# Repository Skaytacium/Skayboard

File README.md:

# Skayboard

## What?

Its **Skay**tacium's key**board**.

## Why? (I get this one a lot)

Good question.

## Layout?

[Here](http://www.keyboard-layout-editor.com/#/gists/023afb41bbd40c8d3c89d3bae84d59ea).

## Really, why?

I couldn't find a keyboard which had this exact layout (some suggested a 60% + numpad, do you think I'm sensible?).  
I also found the pre-existing PCBs too expensive and the open source ones had goofy layouts.  
I'm jobless, stupid and I regret everything.

## And?

- The `sk` keys are macro keys.
- It uses [QMK](https://qmk.fm/).
- Uses [SK6812 Mini-E](https://cdn-shop.adafruit.com/product-files/4960/4960_SK6812MINI-E_REV02_EN.pdf) LEDs, hand solder them if you want to, connection matrix [here](#connections) (because the name starts with SK).
+ The Skaytacium way to build one would be:
  - C<sup>3</sup>Equalz Tangerines, light green (52g)
  - 5mm acrylic plate
  - Stacked crylic and aluminum (layered)
- It took me ~~2~~ 3 years to make this (check earliest commit) because of the global chip shortage and doomerism.

## Details?

### PCB?
- 2 layer
- 355x107 mm
- AVR (32U4), keeping it as simple as possible.
	+ There is no ESD, overcurrent or surge protection on the PCB. I assume all modern electronic USB ports to compensate for that.
- Pads made for handsoldering.
- Curved traces, because the 90s were cool.
- **Not attached to the case in any way, only to the plate, allows for more customizable mounting options.**
- `svg` and `dxf` files for reference are in `lib/gen`.

#### Renders?
- Front

- Back

- Front populated

### Plate?
- Desgined for 5mm plates, but can be used for 3mm-5mm.
	+ 1.5mm should also be possible, but it is strongly not recommended to use that.
- Who am I to tell you though, go crazy with it, `dxf` file is in `lib/gen`.

#### Renders?

### Case?
- Stacked in the following order:
	+ Spacer (L2)
	+ Plate (PCB has no connection to the case)
	+ Spacer (L1)
	+ Spacer (L0)
	+ Case & Logo
- **IMPORTANT:** Spacers L1 and L0 should have atleast 6mm of total height due to the oscillator being an HC49, and that requires 4mm clearance + 1.6mm clearance for PCB thickness.
- **ALSO IMPORTANT:** Either one of spacers L1 or L0 have to be transparent, otherwise you won't be able to see the underglow LEDs (duh). But again, go crazy with it.
- **ALSO SERIOUSLY IMPORTANT:** The `dxf` files do not contain holes for threading, even though the renders show that, you'll have to choose your method of connection, i.e. glue or self-drilled screws. 
- Case & Logo are a single layer since the logo is just an inverse of the case cutout.
- All `dxf` files are in `lib/gen`.

#### Renders?
- Case & Logo

- Full case

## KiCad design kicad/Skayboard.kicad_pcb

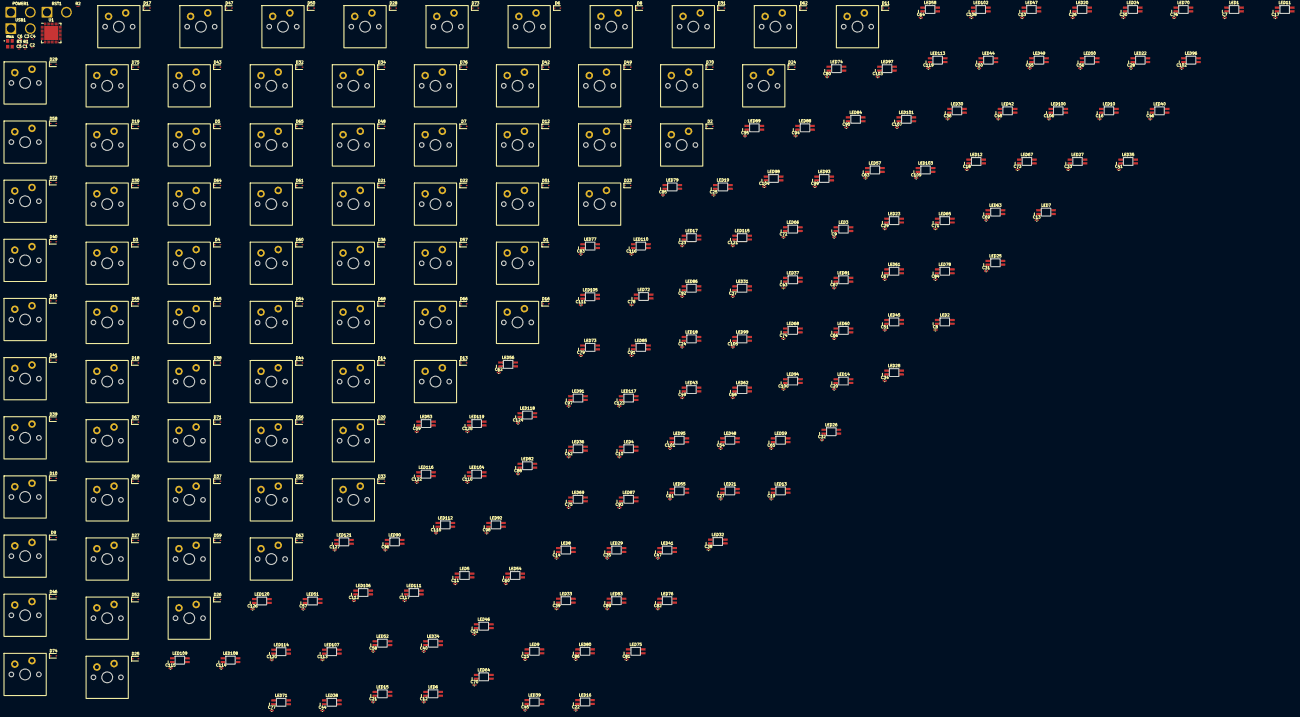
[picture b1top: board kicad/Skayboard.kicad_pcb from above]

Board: 2 copper layers, 408 parts (0 on the bottom side), 153 nets, no tracks yet.

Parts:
C1, C2, C3, C4: 22pF; C_01005_0402Metric
C5: 100nF; C_01005_0402Metric
C6, C7, C8, C9, C10, C11, C12, C13, C14, C15, C16, C17, C18, C19, C20, C21, C22, C23, C24, C25, C26, C27, C28, C29, C30, C31, C32, C33, C34, C35, C36, C37, C38, C39, C40, C41, C42, C43, C44, C45, C46, C47, C48, C49, C50, C51, C52, C53, C54, C55, C56, C57, C58, C59, C60, C61, C62, C63, C64, C65, C66, C67, C68, C69, C70, C71, C72, C73, C74, C75, C76, C77, C78, C79, C80, C81, C82, C83, C84, C85, C86, C87, C88, C89, C90, C91, C92, C93, C94, C95, C96, C97, C98, C99, C100, C101, C102, C103, C104, C105, C106, C107, C108, C109, C110, C111, C112, C113, C114, C115, C116, C117, C118, C119, C120, C121, C122, C123, C124, C125, C126, C127: 100nF; C_0402_1005Metric
D1, D2, D3, D4, D5, D6, D7, D8, D9, D10, D11, D12, D13, D14, D15, D16, D17, D18, D19, D20, D21, D22, D23, D24, D25, D26, D27, D28, D29, D30, D31, D32, D33, D34, D35, D36, D37, D38, D39, D40, D41, D42, D43, D44, D45, D46, D47, D48, D49, D50, D51, D52, D53, D54, D55, D56, D57, D58, D59, D60, D61, D62, D63, D64, D65, D66, D67, D68, D69, D70, D71, D72, D73, D74, D75, D76: 1N4148WS; D_SOD-323
LED1, LED2, LED3, LED4, LED5, LED6, LED7, LED8, LED9, LED10, LED11, LED12, LED13, LED14, LED15, LED16, LED17, LED18, LED19, LED20, LED21, LED22, LED23, LED24, LED25, LED26, LED27, LED28, LED29, LED30, LED31, LED32, LED33, LED34, LED35, LED36, LED37, LED38, LED39, LED40, LED41, LED42, LED43, LED44, LED45, LED46, LED47, LED48, LED49, LED50, LED51, LED52, LED53, LED54, LED55, LED56, LED57, LED58, LED59, LED60, LED61, LED62, LED63, LED64, LED65, LED66, LED67, LED68, LED69, LED70, LED71, LED72, LED73, LED74, LED75, LED76, LED77, LED78, LED79, LED80, LED81, LED82, LED83, LED84, LED85, LED86, LED87, LED88, LED89, LED90, LED91, LED92, LED93, LED94, LED95, LED96, LED97, LED98, LED99, LED100, LED101, LED102, LED103, LED104, LED105, LED106, LED107, LED108, LED109, LED110, LED111, LED112, LED113, LED114, LED115, LED116, LED117, LED118, LED119, LED120, LED121: SK6812MINI-E
MX1, MX2, MX3, MX4, MX5, MX6, MX7, MX8, MX9, MX10, MX11, MX12, MX13, MX14, MX15, MX16, MX17, MX18, MX19, MX20, MX21, MX22, MX23, MX24, MX25, MX26, MX27, MX28, MX29, MX30, MX31, MX32, MX33, MX34, MX35, MX36, MX37, MX38, MX39, MX40, MX41, MX42, MX43, MX44, MX45, MX46, MX47, MX48, MX49, MX50, MX51, MX52, MX53, MX54, MX55, MX56, MX57, MX58, MX59, MX60, MX61, MX62, MX63, MX64, MX65, MX66, MX67, MX68, MX69, MX70, MX71, MX72, MX73, MX74, MX75, MX76: MX
POWER1: Conn_01x02; SolderWire-2.5sqmm_1x02_P7.2mm_D2.4mm_OD3.6mm
R1, R2: 22; R_0201_0603Metric
R3: 10K; R_0201_0603Metric
RST1: Conn_01x02; SolderWire-2.5sqmm_1x02_P7.2mm_D2.4mm_OD3.6mm
U1: ATmega32U4-M; QFN-44-1EP_7x7mm_P0.5mm_EP5.2x5.2mm
USB1: Conn_01x02; SolderWire-2.5sqmm_1x02_P7.2mm_D2.4mm_OD3.6mm
XTAL1: X322516MLB4SI; OSC_X322516MLB4SI

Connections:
/0/DIN: LED10.2 (DOUT), LED11.4 (DIN)
/1/DIN: LED1.2 (DOUT), LED2.4 (DIN)
/1/DOUT: LED2.2 (DOUT), LED3.4 (DIN)
/2/DOUT: LED3.2 (DOUT), LED4.4 (DIN)
/3/DOUT: LED4.2 (DOUT), LED5.4 (DIN)
/4/DOUT: LED5.2 (DOUT), LED6.4 (DIN)
/5/DOUT: LED6.2 (DOUT), LED7.4 (DIN)
/6/DOUT: LED7.2 (DOUT), LED8.4 (DIN)
/7/DOUT: LED8.2 (DOUT), LED9.4 (DIN)
/8/DOUT: LED9.2 (DOUT), LED10.4 (DIN)
/"/DIN: LED49.2 (DOUT), LED50.4 (DIN)
/"/DOUT: LED50.2 (DOUT), LED52.4 (DIN)
/,/DIN: LED67.4 (DIN), LED68.2 (DOUT)
/,/DOUT: LED66.4 (DIN), LED67.2 (DOUT)
/-/DIN: LED11.2 (DOUT), LED12.4 (DIN)
/-/DOUT: LED12.2 (DOUT), LED13.4 (DIN)
/./DIN: LED68.4 (DIN), LED69.2 (DOUT)
/;/DIN: LED48.2 (DOUT), LED49.4 (DIN)
/=/DOUT: LED13.2 (DOUT), LED14.4 (DIN)
/A/DIN: LED40.4 (DIN), LED80.2 (DOUT)
/A/DOUT: LED40.2 (DOUT), LED41.4 (DIN)
/B Slash/DIN: LED33.4 (DIN), LED34.2 (DOUT)
/B Slash/DOUT: LED32.4 (DIN), LED33.2 (DOUT)
/B/DIN: LED64.4 (DIN), LED65.2 (DOUT)
/B/DOUT: LED63.4 (DIN), LED64.2 (DOUT)
/Bksp/DOUT: LED14.2 (DOUT), LED15.4 (DIN)
/C/DIN: LED62.4 (DIN), LED63.2 (DOUT)
/C/DOUT: LED61.4 (DIN), LED62.2 (DOUT)
/COL^{0}: MX1.1 (COL), MX18.1 (COL), MX35.1 (COL), MX51.1 (COL), MX66.1 (COL), U1.18 (PD0)
/COL^{1}: MX2.1 (COL), MX19.1 (COL), MX36.1 (COL), MX52.1 (COL), MX67.1 (COL), U1.19 (PD1)
/COL^{2}: MX3.1 (COL), MX20.1 (COL), MX37.1 (COL), MX53.1 (COL), MX68.1 (COL), U1.20 (PD2)
/COL^{3}: MX4.1 (COL), MX21.1 (COL), MX38.1 (COL), MX54.1 (COL), U1.21 (PD3)
/COL^{4}: MX5.1 (COL), MX22.1 (COL), MX39.1 (COL), MX55.1 (COL), U1.22 (PD5)
/COL^{5}: MX6.1 (COL), MX23.1 (COL), MX40.1 (COL), MX56.1 (COL), MX69.1 (COL), U1.25 (PD4)
/COL^{6}: MX7.1 (COL), MX24.1 (COL), MX41.1 (COL), MX57.1 (COL), U1.37 (PF6)
/COL^{7}: MX8.1 (COL), MX25.1 (COL), MX42.1 (COL), MX58.1 (COL), U1.38 (PF5)
/COL^{8}: MX9.1 (COL), MX26.1 (COL), MX43.1 (COL), MX59.1 (COL), U1.39 (PF4)
/COL^{9}: MX10.1 (COL), MX27.1 (COL), MX44.1 (COL), MX60.1 (COL), MX70.1 (COL), U1.40 (PF1)
/COL^{10}: MX11.1 (COL), MX28.1 (COL), MX45.1 (COL), MX61.1 (COL), MX71.1 (COL), U1.41 (PF0)
/COL^{11}: MX12.1 (COL), MX29.1 (COL), MX46.1 (COL), MX62.1 (COL), MX72.1 (COL), U1.1 (PE6)
/COL^{12}: MX13.1 (COL), MX30.1 (COL), MX47.1 (COL), U1.8 (PB0)
/COL^{13}: MX14.1 (COL), MX31.1 (COL), MX73.1 (COL), U1.9 (PB1)
/COL^{14}: MX15.1 (COL), MX32.1 (COL), MX48.1 (COL), MX63.1 (COL), MX74.1 (COL), U1.10 (PB2)
/COL^{15}: MX16.1 (COL), MX33.1 (COL), MX49.1 (COL), MX64.1 (COL), MX75.1 (COL), U1.11 (PB3)
/COL^{16}: MX17.1 (COL), MX34.1 (COL), MX50.1 (COL), MX65.1 (COL), MX76.1 (COL), U1.12 (PB7)
/Caps/DIN: LED39.2 (DOUT), LED80.4 (DIN)
/D/DIN: LED41.2 (DOUT), LED42.4 (DIN)
/D/DOUT: LED42.2 (DOUT), LED43.4 (DIN)
/Del/DIN: LED34.4 (DIN), LED35.2 (DOUT)
/Down/DIN: LED100.2 (DOUT), LED101.4 (DIN)
/Down/DOUT: LED101.2 (DOUT), LED103.4 (DIN)
/E/DIN: LED23.4 (DIN), LED24.2 (DOUT)
/E/DOUT: LED22.4 (DIN), LED23.2 (DOUT)
/End/DIN: LED35.4 (DIN), LED37.2 (DOUT)
/Enter/DOUT: LED52.2 (DOUT), LED54.4 (DIN)
/Esc/DIN: LED1.4 (DIN), LED20.2 (DOUT)
/F Slash/DIN: LED69.4 (DIN), LED70.2 (DOUT)
/F/DOUT: LED43.2 (DOUT), LED44.4 (DIN)
/G/DOUT: LED44.2 (DOUT), LED45.4 (DIN)
/H/DOUT: LED45.2 (DOUT), LED46.4 (DIN)
/Home/DIN: LED15.2 (DOUT), LED16.4 (DIN)
/Home/DOUT: LED16.2 (DOUT), LED18.4 (DIN)
/I/DIN: LED28.4 (DIN), LED29.2 (DOUT)
/I/DOUT: LED27.4 (DIN), LED28.2 (DOUT)
/J/DOUT: LED46.2 (DOUT), LED47.4 (DIN)
/K/DOUT: LED47.2 (DOUT), LED48.4 (DIN)
/L Alt/DIN: LED81.2 (DOUT), LED83.4 (DIN)
/L Alt/DOUT: LED83.2 (DOUT), LED87.4 (DIN)
/L Ctrl/DOUT: LED59.2 (DOUT), LED81.4 (DIN)
/L Shift/DIN: LED39.4 (DIN), LED60.2 (DOUT)
/LED: LED59.4 (DIN), U1.26 (PD6)
/Left/DIN: LED99.2 (DOUT), LED100.4 (DIN)
/M/DOUT: LED65.4 (DIN), LED66.2 (DOUT)
/Meta/DIN: LED95.2 (DOUT), LED96.4 (DIN)
/Meta/DOUT: LED96.2 (DOUT), LED99.4 (DIN)
/O/DIN: LED29.4 (DIN), LED30.2 (DOUT)
/P/DIN: LED30.4 (DIN), LED31.2 (DOUT)
/PgDn/DIN: LED37.4 (DIN), LED57.2 (DOUT)
/Q/DIN: LED21.4 (DIN), LED22.2 (DOUT)
/Q/DOUT: LED20.4 (DIN), LED21.2 (DOUT)
/R Alt/DIN: LED87.2 (DOUT), LED94.4 (DIN)
/R Alt/DOUT: LED94.2 (DOUT), LED95.4 (DIN)
/R Shift/DIN: LED70.4 (DIN), LED75.2 (DOUT)
/R/DIN: LED24.4 (DIN), LED25.2 (DOUT)
/ROW^{0}: D1.1 (K), D2.1 (K), D3.1 (K), D4.1 (K), D5.1 (K), D6.1 (K), D7.1 (K), D8.1 (K), D9.1 (K), D10.1 (K), D11.1 (K), D12.1 (K), D13.1 (K), D14.1 (K), D15.1 (K), D16.1 (K), D17.1 (K), U1.29 (PB5)
/ROW^{1}: D18.1 (K), D19.1 (K), D20.1 (K), D21.1 (K), D22.1 (K), D23.1 (K), D24.1 (K), D25.1 (K), D26.1 (K), D27.1 (K), D28.1 (K), D29.1 (K), D30.1 (K), D31.1 (K), D32.1 (K), D33.1 (K), D34.1 (K), U1.30 (PB6)
/ROW^{2}: D36.1 (K), D37.1 (K), D38.1 (K), D39.1 (K), D40.1 (K), D41.1 (K), D42.1 (K), D43.1 (K), D44.1 (K), D45.1 (K), D46.1 (K), D47.1 (K), D48.1 (K), D49.1 (K), D50.1 (K), D66.1 (K), U1.31 (PC6)
/ROW^{3}: D35.1 (K), D52.1 (K), D53.1 (K), D54.1 (K), D55.1 (K), D56.1 (K), D57.1 (K), D58.1 (K), D59.1 (K), D60.1 (K), D61.1 (K), D62.1 (K), D63.1 (K), D64.1 (K), D65.1 (K), U1.32 (PC7)
/ROW^{4}: D51.1 (K), D67.1 (K), D68.1 (K), D69.1 (K), D70.1 (K), D71.1 (K), D72.1 (K), D73.1 (K), D74.1 (K), D75.1 (K), D76.1 (K), U1.33 (~HWB/PE2)
/Right/DOUT: LED78.4 (DIN), LED103.2 (DOUT)
/SK1/DOUT: LED54.2 (DOUT), LED55.4 (DIN)
/SK2/DOUT: LED55.2 (DOUT), LED57.4 (DIN)
/SK4/DIN: LED75.4 (DIN), LED76.2 (DOUT)
/SK5/DOUT: LED76.4 (DIN), LED78.2 (DOUT)
/T/DIN: LED25.4 (DIN), LED26.2 (DOUT)
/U/DOUT: LED26.4 (DIN), LED27.2 (DOUT)
/ULED: LED18.2 (DOUT), LED85.4 (DIN)
/ULED1/DOUT: LED17.4 (DIN), LED85.2 (DOUT)
/ULED2/DOUT: LED17.2 (DOUT), LED19.4 (DIN)
/ULED3/DOUT: LED19.2 (DOUT), LED36.4 (DIN)
/ULED4/DOUT: LED36.2 (DOUT), LED38.4 (DIN)
/ULED5/DOUT: LED38.2 (DOUT), LED71.4 (DIN)
/ULED6/DIN: LED51.2 (DOUT), LED53.4 (DIN)
/ULED8/DIN: LED51.4 (DIN), LED71.2 (DOUT)
/ULED10/DIN: LED53.2 (DOUT), LED56.4 (DIN)
/ULED10/DOUT: LED56.2 (DOUT), LED58.4 (DIN)
/ULED11/DIN: LED72.2 (DOUT), LED73.4 (DIN)
/ULED11/DOUT: LED73.2 (DOUT), LED74.4 (DIN)
/ULED12/DIN: LED74.2 (DOUT), LED77.4 (DIN)
/ULED12/DOUT: LED77.2 (DOUT), LED104.4 (DIN)
/ULED13/DIN: LED72.4 (DIN), LED79.2 (DOUT)
/ULED14/DIN: LED58.2 (DOUT), LED79.4 (DIN)
/ULED16/DIN: LED92.4 (DIN), LED105.2 (DOUT)
/ULED16/DOUT: LED91.4 (DIN), LED92.2 (DOUT)
/ULED17/DIN: LED97.4 (DIN), LED98.2 (DOUT)
/ULED17/DOUT: LED97.2 (DOUT), LED105.4 (DIN)
/ULED19/DOUT: LED102.4 (DIN), LED104.2 (DOUT)
/ULED20/DOUT: LED90.4 (DIN), LED91.2 (DOUT)
/ULED21/DOUT: LED98.4 (DIN), LED102.2 (DOUT)
/ULED23/DOUT: LED89.4 (DIN), LED90.2 (DOUT)
/ULED24/DIN: LED84.4 (DIN), LED86.2 (DOUT)
/ULED24/DOUT: LED82.4 (DIN), LED84.2 (DOUT)
/ULED25/DIN: LED88.4 (DIN), LED93.2 (DOUT)
/ULED25/DOUT: LED86.4 (DIN), LED88.2 (DOUT)
/ULED26/DOUT: LED82.2 (DOUT), LED106.4 (DIN)
/ULED27/DIN: LED89.2 (DOUT), LED93.4 (DIN)
/ULED29/DOUT: LED106.2 (DOUT), LED121.4 (DIN)
/ULED31/DIN: LED113.2 (DOUT), LED114.4 (DIN)
/ULED31/DOUT: LED114.2 (DOUT), LED120.4 (DIN)
/ULED32/DIN: LED116.4 (DIN), LED120.2 (DOUT)
/ULED32/DOUT: LED116.2 (DOUT), LED117.4 (DIN)
/ULED34/DIN: LED118.2 (DOUT), LED119.4 (DIN)
/ULED35/DIN: LED112.2 (DOUT), LED113.4 (DIN)
/ULED36/DIN: LED117.2 (DOUT), LED118.4 (DIN)
/ULED38/DIN: LED111.2 (DOUT), LED112.4 (DIN)
/ULED39/DIN: LED107.2 (DOUT), LED108.4 (DIN)
/ULED39/DOUT: LED108.2 (DOUT), LED109.4 (DIN)
/ULED40/DIN: LED109.2 (DOUT), LED110.4 (DIN)
/ULED40/DOUT: LED110.2 (DOUT), LED115.4 (DIN)
/ULED41/DIN: LED107.4 (DIN), LED121.2 (DOUT)
/ULED42/DOUT: LED111.4 (DIN), LED115.2 (DOUT)
/X/DOUT: LED60.4 (DIN), LED61.2 (DOUT)
/[/DIN: LED31.4 (DIN), LED32.2 (DOUT)
GND: C1.1, C2.1, C3.1, C4.1, C5.1, C6.1, C7.1, C8.1, C9.1, C10.1, C11.1, C12.1, C13.1, C14.1, C15.1, C16.1, C17.1, C18.1, C19.1, C20.1, C21.1, C22.1, C23.1, C24.1, C25.1, C26.1, C27.1, C28.1, C29.1, C30.1, C31.1, C32.1, C33.1, C34.1, C35.1, C36.1, C37.1, C38.1, C39.1, C40.1, C41.1, C42.1, C43.1, C44.1, C45.1, C46.1, C47.1, C48.1, C49.1, C50.1, C51.1, C52.1, C53.1, C54.1, C55.1, C56.1, C57.1, C58.1, C59.1, C60.1, C61.1, C62.1, C63.1, C64.1, C65.1, C66.1, C67.1, C68.1, C69.1, C70.1, C71.1, C72.1, C73.1, C74.1, C75.1, C76.1, C77.1, C78.1, C79.1, C80.1, C81.1, C82.1, C83.1, C84.1, C85.1, C86.1, C87.1, C88.1, C89.1, C90.1, C91.1, C92.1, C93.1, C94.1, C95.1, C96.1, C97.1, C98.1, C99.1, C100.1, C101.1, C102.1, C103.1, C104.1, C105.1, C106.1, C107.1, C108.1, C109.1, C110.1, C111.1, C112.1, C113.1, C114.1, C115.1, C116.1, C117.1, C118.1, C119.1, C120.1, C121.1, C122.1, C123.1, C124.1, C125.1, C126.1, C127.1, LED1.3 (VSS), LED2.3 (VSS), LED3.3 (VSS), LED4.3 (VSS), LED5.3 (VSS), LED6.3 (VSS), LED7.3 (VSS), LED8.3 (VSS), LED9.3 (VSS), LED10.3 (VSS), LED11.3 (VSS), LED12.3 (VSS), LED13.3 (VSS), LED14.3 (VSS), LED15.3 (VSS), LED16.3 (VSS), LED17.3 (VSS), LED18.3 (VSS), LED19.3 (VSS), LED20.3 (VSS), LED21.3 (VSS), LED22.3 (VSS), LED23.3 (VSS), LED24.3 (VSS), LED25.3 (VSS), LED26.3 (VSS), LED27.3 (VSS), LED28.3 (VSS), LED29.3 (VSS), LED30.3 (VSS), LED31.3 (VSS), LED32.3 (VSS), LED33.3 (VSS), LED34.3 (VSS), LED35.3 (VSS), LED36.3 (VSS), LED37.3 (VSS), LED38.3 (VSS), LED39.3 (VSS), LED40.3 (VSS), LED41.3 (VSS), LED42.3 (VSS), LED43.3 (VSS), LED44.3 (VSS), LED45.3 (VSS), LED46.3 (VSS), LED47.3 (VSS), LED48.3 (VSS), LED49.3 (VSS), LED50.3 (VSS), LED51.3 (VSS), LED52.3 (VSS), LED53.3 (VSS), LED54.3 (VSS), LED55.3 (VSS), LED56.3 (VSS), LED57.3 (VSS), LED58.3 (VSS), LED59.3 (VSS), LED60.3 (VSS), LED61.3 (VSS), LED62.3 (VSS), LED63.3 (VSS), LED64.3 (VSS), LED65.3 (VSS), LED66.3 (VSS), LED67.3 (VSS), LED68.3 (VSS), LED69.3 (VSS), LED70.3 (VSS), LED71.3 (VSS), LED72.3 (VSS), LED73.3 (VSS), LED74.3 (VSS), LED75.3 (VSS), LED76.3 (VSS), LED77.3 (VSS), LED78.3 (VSS), LED79.3 (VSS), LED80.3 (VSS), LED81.3 (VSS), LED82.3 (VSS), LED83.3 (VSS), LED84.3 (VSS), LED85.3 (VSS), LED86.3 (VSS), LED87.3 (VSS), LED88.3 (VSS), LED89.3 (VSS), LED90.3 (VSS), LED91.3 (VSS), LED92.3 (VSS), LED93.3 (VSS), LED94.3 (VSS), LED95.3 (VSS), LED96.3 (VSS), LED97.3 (VSS), LED98.3 (VSS), LED99.3 (VSS), LED100.3 (VSS), LED101.3 (VSS), LED102.3 (VSS), LED103.3 (VSS), LED104.3 (VSS), LED105.3 (VSS), LED106.3 (VSS), LED107.3 (VSS), LED108.3 (VSS), LED109.3 (VSS), LED110.3 (VSS), LED111.3 (VSS), LED112.3 (VSS), LED113.3 (VSS), LED114.3 (VSS), LED115.3 (VSS), LED116.3 (VSS), LED117.3 (VSS), LED118.3 (VSS), LED119.3 (VSS), LED120.3 (VSS), LED121.3 (VSS), POWER1.2, RST1.2, U1.5 (UGND), U1.15 (GND), U1.23 (GND), U1.35 (GND), U1.43 (GND), U1.45 (GND), XTAL1.2, XTAL1.4
unnamed: C1.2, U1.17 (XTAL1), XTAL1.1
unnamed: C2.2, U1.16 (XTAL2), XTAL1.3
unnamed: C3.2, R1.1, U1.4 (D+)
unnamed: C4.2, R2.1, U1.3 (D-)
unnamed: C5.2, U1.42 (AREF)
unnamed: C6.2, R3.1, RST1.1, U1.13 (~RESET)
unnamed: R1.2, USB1.1
unnamed: R2.2, USB1.2
VCC: C7.2, C8.2, C9.2, C10.2, C11.2, C12.2, C13.2, C14.2, C15.2, C16.2, C17.2, C18.2, C19.2, C20.2, C21.2, C22.2, C23.2, C24.2, C25.2, C26.2, C27.2, C28.2, C29.2, C30.2, C31.2, C32.2, C33.2, C34.2, C35.2, C36.2, C37.2, C38.2, C39.2, C40.2, C41.2, C42.2, C43.2, C44.2, C45.2, C46.2, C47.2, C48.2, C49.2, C50.2, C51.2, C52.2, C53.2, C54.2, C55.2, C56.2, C57.2, C58.2, C59.2, C60.2, C61.2, C62.2, C63.2, C64.2, C65.2, C66.2, C67.2, C68.2, C69.2, C70.2, C71.2, C72.2, C73.2, C74.2, C75.2, C76.2, C77.2, C78.2, C79.2, C80.2, C81.2, C82.2, C83.2, C84.2, C85.2, C86.2, C87.2, C88.2, C89.2, C90.2, C91.2, C92.2, C93.2, C94.2, C95.2, C96.2, C97.2, C98.2, C99.2, C100.2, C101.2, C102.2, C103.2, C104.2, C105.2, C106.2, C107.2, C108.2, C109.2, C110.2, C111.2, C112.2, C113.2, C114.2, C115.2, C116.2, C117.2, C118.2, C119.2, C120.2, C121.2, C122.2, C123.2, C124.2, C125.2, C126.2, C127.2, LED1.1 (VDD), LED2.1 (VDD), LED3.1 (VDD), LED4.1 (VDD), LED5.1 (VDD), LED6.1 (VDD), LED7.1 (VDD), LED8.1 (VDD), LED9.1 (VDD), LED10.1 (VDD), LED11.1 (VDD), LED12.1 (VDD), LED13.1 (VDD), LED14.1 (VDD), LED15.1 (VDD), LED16.1 (VDD), LED17.1 (VDD), LED18.1 (VDD), LED19.1 (VDD), LED20.1 (VDD), LED21.1 (VDD), LED22.1 (VDD), LED23.1 (VDD), LED24.1 (VDD), LED25.1 (VDD), LED26.1 (VDD), LED27.1 (VDD), LED28.1 (VDD), LED29.1 (VDD), LED30.1 (VDD), LED31.1 (VDD), LED32.1 (VDD), LED33.1 (VDD), LED34.1 (VDD), LED35.1 (VDD), LED36.1 (VDD), LED37.1 (VDD), LED38.1 (VDD), LED39.1 (VDD), LED40.1 (VDD), LED41.1 (VDD), LED42.1 (VDD), LED43.1 (VDD), LED44.1 (VDD), LED45.1 (VDD), LED46.1 (VDD), LED47.1 (VDD), LED48.1 (VDD), LED49.1 (VDD), LED50.1 (VDD), LED51.1 (VDD), LED52.1 (VDD), LED53.1 (VDD), LED54.1 (VDD), LED55.1 (VDD), LED56.1 (VDD), LED57.1 (VDD), LED58.1 (VDD), LED59.1 (VDD), LED60.1 (VDD), LED61.1 (VDD), LED62.1 (VDD), LED63.1 (VDD), LED64.1 (VDD), LED65.1 (VDD), LED66.1 (VDD), LED67.1 (VDD), LED68.1 (VDD), LED69.1 (VDD), LED70.1 (VDD), LED71.1 (VDD), LED72.1 (VDD), LED73.1 (VDD), LED74.1 (VDD), LED75.1 (VDD), LED76.1 (VDD), LED77.1 (VDD), LED78.1 (VDD), LED79.1 (VDD), LED80.1 (VDD), LED81.1 (VDD), LED82.1 (VDD), LED83.1 (VDD), LED84.1 (VDD), LED85.1 (VDD), LED86.1 (VDD), LED87.1 (VDD), LED88.1 (VDD), LED89.1 (VDD), LED90.1 (VDD), LED91.1 (VDD), LED92.1 (VDD), LED93.1 (VDD), LED94.1 (VDD), LED95.1 (VDD), LED96.1 (VDD), LED97.1 (VDD), LED98.1 (VDD), LED99.1 (VDD), LED100.1 (VDD), LED101.1 (VDD), LED102.1 (VDD), LED103.1 (VDD), LED104.1 (VDD), LED105.1 (VDD), LED106.1 (VDD), LED107.1 (VDD), LED108.1 (VDD), LED109.1 (VDD), LED110.1 (VDD), LED111.1 (VDD), LED112.1 (VDD), LED113.1 (VDD), LED114.1 (VDD), LED115.1 (VDD), LED116.1 (VDD), LED117.1 (VDD), LED118.1 (VDD), LED119.1 (VDD), LED120.1 (VDD), LED121.1 (VDD), POWER1.1, R3.2, U1.2 (UVCC), U1.6 (UCAP), U1.7 (VBUS), U1.14 (VCC), U1.24 (AVCC), U1.34 (VCC), U1.44 (AVCC)

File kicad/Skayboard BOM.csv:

"Reference","Value","Datasheet","Footprint","Qty","DNP"
"C1,C6,C7,C8,C9,C10,C11,C12,C13,C14,C15,C16,C17,C18,C19,C20,C21,C22,C23,C24,C25,C26,C27,C28,C29,C30,C31,C32,C33,C34,C35,C36,C37,C38,C39,C40,C41,C42,C43,C44,C45,C46,C47,C48,C49,C50,C51,C52,C53,C54,C55,C56,C57,C58,C59,C60,C61,C62,C63,C64,C65,C66,C67,C68,C69,C70,C71,C72,C73,C74,C75,C76,C77,C78,C79,C80,C81,C82,C83,C84,C85,C86,C87,C88,C89,C90,C91,C92,C93,C94,C95,C96,C97,C98,C99,C100,C101,C102,C103,C104,C105,C106,C107,C108,C109,C110,C111,C112,C113,C114,C115,C116,C117,C118,C119,C120,C121,C122,C123,C124,C125,C126,C127,C128","100nF","~","Capacitor_SMD:C_0402_1005Metric_Pad0.74x0.62mm_HandSolder","124",""
"C2,C4","22pF","~","Capacitor_SMD:C_0402_1005Metric_Pad0.74x0.62mm_HandSolder","2",""
"C3","1uF","~","Capacitor_SMD:C_0603_1608Metric_Pad1.08x0.95mm_HandSolder","1",""
"C5","10uF","~","Capacitor_SMD:C_0603_1608Metric_Pad1.08x0.95mm_HandSolder","1",""
"D1,D2,D3,D4,D5,D6,D7,D8,D9,D10,D11,D12,D13,D14,D15,D16,D17,D18,D19,D20,D21,D22,D23,D24,D25,D26,D27,D28,D29,D30,D31,D32,D33,D34,D35,D36,D37,D38,D39,D40,D41,D42,D43,D44,D45,D46,D47,D48,D49,D50,D51,D52,D53,D54,D55,D56,D57,D58,D59,D60,D61,D62,D63,D64,D65,D66,D67,D68,D69,D70,D71,D72,D73,D74,D75,D76","1N4148WS","https://www.vishay.com/docs/85751/1n4148ws.pdf","Diode_SMD:D_SOD-323_HandSoldering","76",""
"LED1,LED2,LED3,LED4,LED5,LED6,LED7,LED8,LED9,LED10,LED11,LED12,LED13,LED14,LED15,LED16,LED17,LED18,LED19,LED20,LED21,LED22,LED23,LED24,LED25,LED26,LED27,LED28,LED29,LED30,LED31,LED32,LED33,LED34,LED35,LED36,LED37,LED38,LED39,LED40,LED41,LED42,LED43,LED44,LED45,LED46,LED47,LED48,LED49,LED50,LED51,LED52,LED53,LED54,LED55,LED56,LED57,LED58,LED59,LED60,LED61,LED62,LED63,LED64,LED65,LED66,LED67,LED68,LED69,LED70,LED71,LED72,LED73,LED74,LED75,LED76,LED77,LED78,LED79,LED80,LED81,LED82,LED83,LED84,LED85,LED86,LED87,LED88,LED89,LED90,LED91,LED92,LED93,LED94,LED95,LED96,LED97,LED98,LED99,LED100,LED101,LED102,LED103,LED104,LED105,LED106,LED107,LED108,LED109,LED110,LED111,LED112,LED113,LED114,LED115,LED116,LED117,LED118,LED119,LED120","SK6812MINI-E","https://cdn-shop.adafruit.com/product-files/4960/4960_SK6812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","Skayboard:SK6812MINI-E","120","DNP"
"POWER1,RST1,USB1","Conn_01x02","~","Connector_Wire:SolderWire-2.5sqmm_1x02_P7.2mm_D2.4mm_OD3.6mm","3","DNP"
"R1","10K","~","Resistor_SMD:R_0603_1608Metric_Pad0.98x0.95mm_HandSolder","1",""
"R2,R3","22","~","Resistor_SMD:R_0603_1608Metric_Pad0.98x0.95mm_HandSolder","2",""
"U1","ATmega32U4-A","http://ww1.microchip.com/downloads/en/DeviceDoc/Atmel-7766-8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","Package_QFP:TQFP-44_10x10mm_P0.8mm","1",""
"Y1","16MHz","~","Crystal:Crystal_HC49-U_Vertical","1",""

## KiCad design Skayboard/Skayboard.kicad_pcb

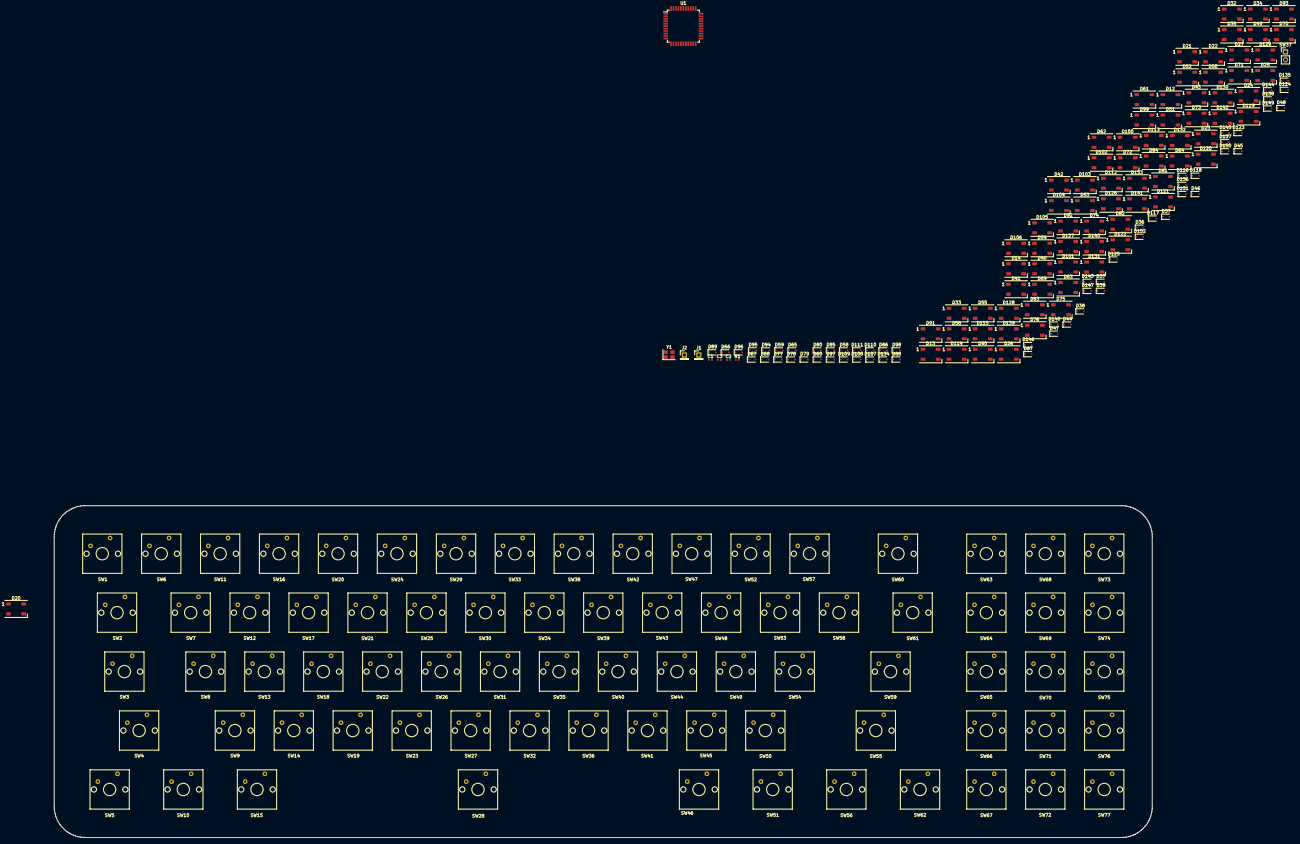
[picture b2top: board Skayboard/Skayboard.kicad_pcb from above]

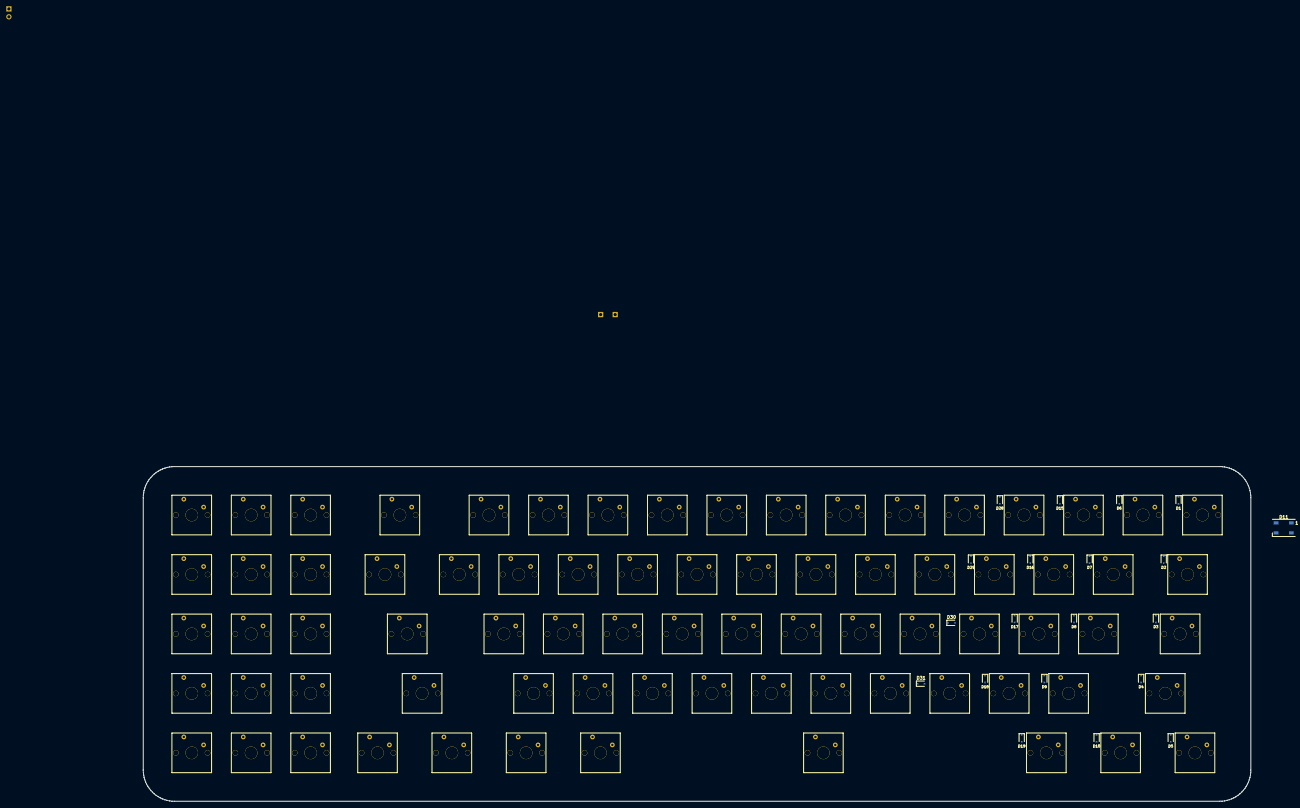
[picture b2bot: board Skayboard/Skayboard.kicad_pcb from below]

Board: 2 copper layers, 354.9 x 107.3 mm, 237 parts (20 on the bottom side), 180 nets, no tracks yet.

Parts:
C1, C2: 22pF; C_0402_1005Metric
C3: 100nF; C_0402_1005Metric
D1, D2, D3, D4, D5, D6, D7, D8, D9, D10, D15, D16, D17, D18, D19, D28, D29, D30, D31, D36, D37, D38, D39, D44, D45, D46, D47, D48, D57, D58, D59, D60, D65, D66, D67, D68, D77, D78, D79, D80, D85, D86, D87, D88, D89, D94, D95, D96, D97, D98, D107, D108, D109, D110, D111, D116, D117, D118, D123, D124, D125, D134, D135, D136, D137, D138, D143, D144, D145, D146, D147, D148, D149, D150, D151, D152: 1N4148; D_SOD-323F
D11, D12, D13, D14, D20, D21, D22, D23, D24, D25, D26, D27, D32, D33, D34, D35, D40, D41, D42, D43, D49, D50, D51, D52, D53, D54, D55, D56, D61, D62, D63, D64, D69, D70, D71, D72, D73, D74, D75, D76, D81, D82, D83, D84, D90, D91, D92, D93, D99, D100, D101, D102, D103, D104, D105, D106, D112, D113, D114, D115, D119, D120, D121, D122, D126, D127, D128, D129, D130, D131, D132, D133, D139, D140, D141, D142: WS2812B; LED_WS2812B_PLCC4_5.0x5.0mm_P3.2mm
J1: D+; PinHeader_1x01_P2.54mm_Vertical
J2: D-; PinHeader_1x01_P2.54mm_Vertical
R1: R; R_0402_1005Metric
SW1, SW2, SW3, SW4, SW5, SW6, SW7, SW8, SW9, SW10, SW11, SW12, SW13, SW14, SW15, SW16, SW17, SW18, SW19, SW20, SW21, SW22, SW23, SW24, SW25, SW26, SW27, SW28, SW29, SW30, SW31, SW32, SW33, SW34, SW35, SW36, SW38, SW39, SW40, SW41, SW42, SW43, SW44, SW45, SW46, SW47, SW48, SW49, SW50, SW51, SW52, SW53, SW54, SW55, SW56, SW57, SW58, SW59, SW60, SW61, SW62, SW63, SW64, SW65, SW66, SW67, SW68, SW69, SW70, SW71, SW72, SW73, SW74, SW75, SW76, SW77: C3 Tangerine; Cherry MX
SW37: RST; PinHeader_1x02_P2.54mm_Vertical
U1: ATmega32U4-AU; TQFP-44_10x10mm_P0.8mm
Y1: 16MHz; Crystal_SMD_SeikoEpson_FA238-4Pin_3.2x2.5mm

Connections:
+5V: D12.1, D13.1, D14.1, D20.1, D21.1, D22.1, D23.1, D24.1, D25.1, D26.1, D27.1, D32.1, D33.1, D34.1, D35.1, D40.1, D41.1, D42.1, D43.1, D49.1, D50.1, D51.1, D52.1, D53.1, D54.1, D55.1, D56.1, D61.1, D62.1, D63.1, D64.1, D69.1, D70.1, D71.1, D72.1, D73.1, D74.1, D75.1, D76.1, D81.1, D82.1, D83.1, D84.1, D90.1, D91.1, D92.1, D93.1, D99.1, D100.1, D101.1, D102.1, D103.1, D104.1, D105.1, D106.1, D112.1, D113.1, D114.1, D115.1, D119.1, D120.1, D121.1, D122.1, D126.1, D127.1, D128.1, D129.1, D130.1, D131.1, D132.1, D133.1, D139.1, D140.1, D141.1, D142.1, R1.1, U1.2, U1.6, U1.7, U1.14, U1.24, U1.34, U1.44
COL0: SW1.1, SW2.1, SW3.1, SW4.1, SW5.1
COL1: SW6.1, SW7.1, SW8.1, SW9.1, SW10.1
COL2: SW11.1, SW12.1, SW13.1, SW14.1, SW15.1
COL3: SW16.1, SW17.1, SW18.1, SW19.1
COL4: SW20.1, SW21.1, SW22.1, SW23.1
COL5: SW24.1, SW25.1, SW26.1, SW27.1, SW28.1
COL6: SW29.1, SW30.1, SW31.1, SW32.1
COL7: SW33.1, SW34.1, SW35.1, SW36.1
COL8: SW38.1, SW39.1, SW40.1, SW41.1
COL9: SW42.1, SW43.1, SW44.1, SW45.1, SW46.1
COL10: SW47.1, SW48.1, SW49.1, SW50.1, SW51.1
COL11: SW52.1, SW53.1, SW54.1, SW55.1, SW56.1
COL12: SW57.1, SW58.1, SW59.1
COL13: SW60.1, SW61.1, SW62.1
COL14: SW63.1, SW64.1, SW65.1, SW66.1, SW67.1
COL15: SW68.1, SW69.1, SW70.1, SW71.1, SW72.1
COL16: SW73.1, SW74.1, SW75.1, SW76.1, SW77.1
GND: C1.2, C2.2, C3.2, D12.3, D13.3, D14.3, D20.3, D21.3, D22.3, D23.3, D24.3, D25.3, D26.3, D27.3, D32.3, D33.3, D34.3, D35.3, D40.3, D41.3, D42.3, D43.3, D49.3, D50.3, D51.3, D52.3, D53.3, D54.3, D55.3, D56.3, D61.3, D62.3, D63.3, D64.3, D69.3, D70.3, D71.3, D72.3, D73.3, D74.3, D75.3, D76.3, D81.3, D82.3, D83.3, D84.3, D90.3, D91.3, D92.3, D93.3, D99.3, D100.3, D101.3, D102.3, D103.3, D104.3, D105.3, D106.3, D112.3, D113.3, D114.3, D115.3, D119.3, D120.3, D121.3, D122.3, D126.3, D127.3, D128.3, D129.3, D130.3, D131.3, D132.3, D133.3, D139.3, D140.3, D141.3, D142.3, SW37.1, U1.5, U1.15, U1.23, U1.35, U1.43, Y1.2, Y1.4
unnamed: C1.1, U1.17, Y1.3
unnamed: C2.1, U1.16, Y1.1
unnamed: C3.1, U1.42
unnamed: D1.2, SW1.2
unnamed: D2.2, SW2.2
unnamed: D3.2, SW3.2
unnamed: D4.2, SW4.2
unnamed: D5.2, SW5.2
unnamed: D6.2, SW6.2
unnamed: D7.2, SW7.2
unnamed: D8.2, SW8.2
unnamed: D9.2, SW9.2
unnamed: D10.2, SW10.2
unnamed: D12.2, D21.4
unnamed: D12.4, D139.2
unnamed: D13.2, D22.4
unnamed: D13.4, D140.2
unnamed: D14.2, D23.4
unnamed: D14.4, D141.2
unnamed: D15.2, SW11.2
unnamed: D16.2, SW12.2
unnamed: D17.2, SW13.2
unnamed: D18.2, SW14.2
unnamed: D19.2, SW15.2
unnamed: D20.2, D24.4
unnamed: D21.2, D25.4
unnamed: D22.2, D26.4
unnamed: D23.2, D27.4
unnamed: D24.2, D32.4
unnamed: D25.2, D33.4
unnamed: D26.2, D34.4
unnamed: D27.2, D35.4
unnamed: D28.2, SW16.2
unnamed: D29.2, SW17.2
unnamed: D30.2, SW18.2
unnamed: D31.2, SW19.2
unnamed: D32.2, D40.4
unnamed: D33.2, D41.4
unnamed: D34.2, D42.4
unnamed: D35.2, D43.4
unnamed: D36.2, SW20.2
unnamed: D37.2, SW21.2
unnamed: D38.2, SW22.2
unnamed: D39.2, SW23.2
unnamed: D40.2, D49.4
unnamed: D41.2, D50.4
unnamed: D42.2, D51.4
unnamed: D43.2, D52.4
unnamed: D44.2, SW24.2
unnamed: D45.2, SW25.2
unnamed: D46.2, SW26.2
unnamed: D47.2, SW27.2
unnamed: D48.2, SW28.2
unnamed: D49.2, D53.4
unnamed: D50.2, D54.4
unnamed: D51.2, D55.4
unnamed: D52.2, D56.4
unnamed: D53.2, D61.4
unnamed: D54.2, D62.4
unnamed: D55.2, D63.4
unnamed: D56.2, D64.4
unnamed: D57.2, SW29.2
unnamed: D58.2, SW30.2
unnamed: D59.2, SW31.2
unnamed: D60.2, SW32.2
unnamed: D61.2, D69.4
unnamed: D62.2, D70.4
unnamed: D63.2, D71.4
unnamed: D64.2, D72.4
unnamed: D65.2, SW33.2
unnamed: D66.2, SW34.2
unnamed: D67.2, SW35.2
unnamed: D68.2, SW36.2
unnamed: D69.2, D73.4
unnamed: D70.2, D74.4
unnamed: D71.2, D75.4
unnamed: D72.2, D76.4
unnamed: D73.2, D81.4
unnamed: D74.2, D82.4
unnamed: D75.2, D83.4
unnamed: D76.2, D84.4
unnamed: D77.2, SW38.2
unnamed: D78.2, SW39.2
unnamed: D79.2, SW40.2
unnamed: D80.2, SW41.2
unnamed: D81.2, D90.4
unnamed: D82.2, D91.4
unnamed: D83.2, D92.4
unnamed: D84.2, D93.4
unnamed: D85.2, SW42.2
unnamed: D86.2, SW43.2
unnamed: D87.2, SW44.2
unnamed: D88.2, SW45.2
unnamed: D89.2, SW46.2
unnamed: D90.2, D99.4
unnamed: D94.2, SW47.2
unnamed: D95.2, SW48.2
unnamed: D96.2, SW49.2
unnamed: D97.2, SW50.2
unnamed: D98.2, SW51.2
unnamed: D100.2, D104.4
unnamed: D91.2, D100.4
unnamed: D101.2, D105.4
unnamed: D92.2, D101.4
unnamed: D102.2, D106.4
unnamed: D93.2, D102.4
unnamed: D103.2, D112.4
unnamed: D99.2, D103.4
unnamed: D104.2, D113.4
unnamed: D105.2, D114.4
unnamed: D106.2, D115.4
unnamed: D107.2, SW52.2
unnamed: D108.2, SW53.2
unnamed: D109.2, SW54.2
unnamed: D110.2, SW55.2
unnamed: D111.2, SW56.2
unnamed: D112.2, D119.4
unnamed: D113.2, D120.4
unnamed: D114.2, D121.4
unnamed: D115.2, D122.4
unnamed: D116.2, SW57.2
unnamed: D117.2, SW58.2
unnamed: D118.2, SW59.2
unnamed: D119.2, D126.4
unnamed: D120.2, D127.4
unnamed: D121.2, D128.4
unnamed: D122.2, D129.4
unnamed: D123.2, SW60.2
unnamed: D124.2, SW61.2
unnamed: D125.2, SW62.2
unnamed: D126.2, D130.4
unnamed: D127.2, D131.4
unnamed: D128.2, D132.4
unnamed: D129.2, D133.4
unnamed: D130.2, D139.4
unnamed: D131.2, D140.4
unnamed: D132.2, D141.4
unnamed: D133.2, D142.4
unnamed: D134.2, SW63.2
unnamed: D135.2, SW64.2
unnamed: D136.2, SW65.2
unnamed: D137.2, SW66.2
unnamed: D138.2, SW67.2
unnamed: D143.2, SW68.2
unnamed: D144.2, SW69.2
unnamed: D145.2, SW70.2
unnamed: D146.2, SW71.2
unnamed: D147.2, SW72.2
unnamed: D148.2, SW73.2
unnamed: D149.2, SW74.2
unnamed: D150.2, SW75.2
unnamed: D151.2, SW76.2
unnamed: D152.2, SW77.2
unnamed: J1.1, U1.4
unnamed: J2.1, U1.3
unnamed: R1.2, SW37.2, U1.13
ROW0: D1.1, D6.1, D15.1, D28.1, D36.1, D44.1, D57.1, D65.1, D77.1, D85.1, D94.1, D107.1, D116.1, D123.1, D134.1, D143.1, D148.1
ROW1: D2.1, D7.1, D16.1, D29.1, D37.1, D45.1, D58.1, D66.1, D78.1, D86.1, D95.1, D108.1, D117.1, D124.1, D135.1, D144.1, D149.1
ROW2: D3.1, D8.1, D17.1, D30.1, D38.1, D46.1, D59.1, D67.1, D79.1, D87.1, D96.1, D109.1, D118.1, D136.1, D145.1, D150.1
ROW3: D4.1, D9.1, D18.1, D31.1, D39.1, D47.1, D60.1, D68.1, D80.1, D88.1, D97.1, D110.1, D137.1, D146.1, D151.1
ROW4: D5.1, D10.1, D19.1, D48.1, D89.1, D98.1, D111.1, D125.1, D138.1, D147.1, D152.1

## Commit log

2020-10-27 Late initial commit
2020-10-27 Better directory tree and README
2020-10-27 Added gitbat for easier gitting
2020-10-28 Keys arranged, partially labelled
2020-10-28 More key work
2020-10-30 Added new footprint and changed symbol
2020-10-30 More useless history deletion
2020-10-30 storing commit
2020-10-30 Changed schematic size
2020-10-30 Changed BOM and schematic symbol
2020-10-30 Changed symbol, minor changes
2020-10-30 storing change
2020-10-30 Added nets to the component
2020-10-31 Switches placed and routed, pcb outline created.
2020-10-31 Stashing commit
2020-10-31 Removed history
2020-11-01 Cleaned history and updated schematic
2020-11-03 PCB lib inspected, pad pin numbers changed to non conflicting ones.
2020-11-03 Changed footprint and schematic
2020-11-03 Symbol-footprint link sorted out (next time set symbol library type to 'standard' not 'mechanical', otherwise footprint linking will not be possible)
2020-11-03 added LICENSE
2020-11-03 Changed project settings, added LICENSE
2020-11-03 switches reposition in pcb, errors removed
2020-11-03 Changed plate, removed history, updated schematic and PCB
2020-11-04 Switches perfectly aligned, locked in place
2020-11-04 Wired switch row and columns
2020-11-05 Microcontroller peripheral components laid out
2020-11-05 Added stabilizer footprints and stabilizers
2020-11-05 Wiring R/C done and designator fix
2020-11-05 Major changes to LED wiring for easy routing
2020-11-05 Added diode to footprint
2020-11-05 Major changes to PCB
    Footprint has been updated and diode is on the
    bottom side now. PCB wiring is being redone and
    updating schematics and footprints constantly.
2020-11-08 New footprint, tried to do stuff
2020-11-09 schematic cleaned up, footprint updated
2020-11-12 Major changes
    Added rows to the PCB, mirrored the LEDs for easy connection and added a new schematic symbol in the library for the mirrored LED. Added some VCC connections.
2020-11-13 Updated PCB traces
2020-11-15 Four layers enabled, ground plane added, microcontroller placed
2020-11-15 Wired the uC a little more
2020-12-14 Too lazy to note changes, but deleted history and rev3 has begun
2020-12-14 Few changes
    -Rev 3 started completely, Rev 2 is removed from project.
    -Cleaned up schematic (changed a few key wirings, TODO: uC pinout).
    -Finished tracing the LEDs, starting columns/rows
2020-12-14 Big changes
    -Wired rows and columns
    -Changed stabilizer footprint
    -Removed stupid bulk
2020-12-14 Connected VCC, might have to redo due to uC stuff
2020-12-15 Initial Kicad Commit
2020-12-15 Decent changes
    -Removed columns
    -Changed footprints
    -Don't want to start over again
2020-12-15 Man finna updated footprints
2020-12-15 Cleaned up the repo, A LOT
2020-12-15 Cleaned up repo again?
2020-12-15 Gitignore is ignoring me
2020-12-15 Switches placed and aligned, diodes halfway done.
2020-12-15 Cleaned up repo properly
2020-12-15 Cleaned up repo
2020-12-15 Started column wiring, finished VCC wiring
2020-12-15 Finished column wiring, connected all VCCs
2020-12-15 Diodes placed, first row of LEDs almost done
2020-12-15 Refined gitignore further and saved project
2020-12-16 Major changes
    - Cleaned up wiring
    - Added a new schematic symbol and PCB symbol for an oscillator so that I can order a cheaper part.
    - PCB Designing is pain
    - Started uC wiring
2020-12-16 Major Changes
    -Almost finished uC wiring
    (Need to rotate uC, add oscillator, start column/row connections)
    -Enhanced footprints further
    -Made USB connections
    -Finally
2020-12-16 Merging is hard
2020-12-16 Renamed old files, changed nothing
2020-12-16 Columns 0 to 5 wired, doing 12 to 16.
2020-12-16 JUST TWO GODDAMN COLUMS LEFT AND SID IS LIKE "COMMITCOMMITCOMMIT"
2020-12-16 Columns completed.
2020-12-17 Decent changes
    - Cleaned up wiring
    - Finished LED wiring
    - Updating schematic and doing rows
2020-12-17 Almost
    -Schematic update needed
    -Underglow, soon
    -Oscillator (still haven't done it)
2020-12-18 Updates
    -Cleaned up bunch of traces
    -Better via placement
    -VCC connected to USB
    -Nets cleared
    TODO: Update schematic (very petty), oscillator, underglow
2020-12-18 Crystal placed, logo and credits made a little bigger, row nets assigned.
2020-12-18 Major changes
    - Added test points for unused pins
    - Cleaned oscillator because NNNI wired it
    - Made a little space for underglow
    - Sent JLCPCB an email
2020-12-18 Petty changes
2020-12-25 Started rev4, updated footprints
2020-12-26 Started LED rewiring
2020-12-26 Finished shift to sk6812, maybe
2020-12-26 Major changes
    -Midway through VCC wiring
    -About to start on underglow
2020-12-26 Finished vcc rewiring
2020-12-26 Bug fixes?
2020-12-26 Major changes
    -Started normal LED footprint
    -Rough underglow positioning done
    -Added silkscreen
    -Few things to be changed
2020-12-27 Big changes
    -Made new footprint
    -Squashed some bugs
    -Started underglow
    -Schematic updated
    -Added some keepouts
    -Cleaned stuff up
2020-12-27 Finished 2/4 placement
2020-12-27 Decent changes
    -Finished equation for placing LEDs
    -One coordinate for each side done
    -Saved project
2020-12-27 Finished underglow placement
2020-12-27 LED data wiring done
2020-12-27 Everything done
    TODO: Ground Plane, Checking
2020-12-28 Major changes
    -Ground plane v0.6.9 done
    -Cleaned up a lot of DRC errors
    -Cleared some shorts in footprints
    -Removed crap silkscreen
    -Better LED pads
    -Added ground vias
2020-12-28 Saved project
2020-12-28 Added the best 3D models
2020-12-30 Major changes
    - First build done, gerber outputs look fine
    - Cleaned up designators
    - Better schematic library
    - About to start work with the Pick and place and BOM files
    - Getting there very soon
2020-12-31 Major changes
    -Added an OutputJob file to automate production
    -Adding version numbers to each entry
    -Cleaned folder directory
    -Outputs can now be found in the Revision folder, e.g. Rev4
    -P&P and BOM files will be handled seperately
2020-12-31 Decent changes
    -Better output job
    -Better BOM
    TODO: Make BOM and P&P JLCPCB compatible
2021-01-01 Rev5...
    I'm too tired to put more commit messages here, rev5 is starting, this
    time I will add versions and all that good shit, plus everything will be
    integrated in altium so that my brain doesn't melt trying to place
    reference offsets in Excel.
    Sanity is also down to 5%
2021-01-01 Cleaned up way too much stuff
2021-01-01 Starting new branches for each rev
2021-01-01 Made seperate rev3 branch
2021-01-01 Made rev4 branch
2021-01-01 Rev5 File Struct
2021-01-01 Even better file structure
2021-01-01 Projext structure done, starting
2021-01-01 I'm taking a break
2021-02-18 marco != macro
2021-04-19 Skaytacium returns
2021-05-16 Skayboard returns from the dead/1?!??!?!
2021-05-21 Oh boy here we go again aka Rev6
2021-05-21 Epic Rev6 moment
2021-05-24 6.1.0; Library refactor; Big;
    Finally some progress.
    - Cleaned up the PCB and SCH libs
    - Better part descriptors
    - Added more detail and removed unnecessary garbage
    - Epic
2021-05-25 6.2.0; Massive changes
    - Redesigned the entire library thing
    - Started schematic again
    - Cleaned MCU schematic
    - Cleaned SchLib
    - Cleaned PcbLib
    - Better pinouts
2021-05-26 Final schematic except underglow
    - Nice
2021-05-26 More schematic stuff
2021-05-28 6.2.0; Decent
    Better schematic, starting work on PCB and other weird stuff.
2021-05-30 Started PCB work
2021-05-30 bruh moment
2021-06-29 It works?!??!?!?
2021-06-30 Whoa, progress
2021-07-03 TOMORROW IS ORDER DAY
2021-07-03 Stuff
    LED and Key aligning done, cap and diode is remaining.
    i'll probably hand over the palcement of keys to NNNI lmao
2021-07-03 Time for NNNI to worok
2021-07-04 Stuff
    Re-imported the DXF and added crosses to it so i can align switches
    perfectly.
    Stabilisers seem to be perfectly aligned, even if they aren't i'll make
    them.
2021-07-04 UASHIDUAHSD
2021-07-04 Preliminary checks done, NNNI WORK
2021-07-04 Keys reversed
2021-07-04 Adding underglow
2021-07-05 Started underglow, oh boy
2021-07-11 MAN WHY ARE THESE LEDS SO STUPID
2021-07-26 KILL ME END MY SUFFERING
2021-07-26 REVISION FRICKING SEVENNNNNN
2021-07-26 might give up
2021-07-27 BUNCH OF STUFF INEFFICNEIT ASODIOSDJ
2021-07-27 Placed keys
2021-07-27 Footprint aligning and wiring done
2021-07-27 Added Stabs
2021-07-27 Started PCB, Finished LED tracing
    Bunch of additiosn
    Schematic redesigned because i messed up
2021-07-27 bruh rows and LED wiring done?!?!?!
2021-07-27 stuff
2021-07-27 LED stuff
2021-07-27 Major work on columns
2021-07-27 First VCC row done and VCC Vias placed
2021-07-27 VCC for SKLEDs done
2021-07-27 Dimmin + some vcc
2021-07-27 MCU and the decouplers
2021-07-27 MCU DONE BRUH LETS GO
2021-07-28 MCU VCC and GND, starting ULEDs
2021-07-28 INFINITE PROGRESS ON UNDERGLOW BRUHH
2021-07-28 Underglow perfected...
2021-07-28 ULED VCC done
2021-07-28 more uled VCC lmao
2021-07-29 Row to MCU
2021-07-29 Forgot what i did but heres a commit
2021-07-29 almost all mcu connections done
2021-07-29 almosT THERE BRUH LETS GO
2021-07-29 more cleanup
2021-07-29 bruh underglow done
2021-07-29 frick lmao
2021-07-29 capacitors on bottom side now
    updated output job file too
2021-07-29 grounding and plane done, last thing is DRC
2021-07-29 Ran DRC, cleaned stuff
2021-07-30 Finished skayboard....
2021-07-30 Final cleanup
2021-07-30 Definitely final cleanup lmao
2022-06-07 big things are about to happen
2022-06-07 feat: makes the README readable
2022-06-07 fix: changes ordering and seperators
2022-06-07 feat: kicad
2022-06-07 fix: adds link for LEDs in README
2022-06-07 feat: finishes key layout
2022-06-08 feat: finishes schematic, starts work on PCB
2022-07-11 save: going back to windows...
2024-05-25 fix: removes altium
2024-07-29 Outro - M83
2024-08-22 Skayboard, v1
2024-08-22 doc: fixes README links
